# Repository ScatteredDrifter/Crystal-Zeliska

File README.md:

# Crystal-Zeliska
---
##### <div align="right">Created and designed by: Fabian.S || ScatteredDrifter
</div>
<br />
<br/>
Welcome my first attempt to design a orthogonal split-keyboard. 

This is a 62-key-keyboard with 31 1u keys per side. 

The PCB was designed to be usable for both the left and right side. 

## Features: 
 - offers OLED - SSD1306 - display support, at least in theory **#** *haven't tested it yet* 
 - eight ws2812b mounted RGB LEds for underglow around the keyboard
 - included files for bottom and top-plate for FR4 skeleton mounting method

## Planned Features: 

- QMK support
- updated PCB with support pimoroni trackball 
- support for rotary encoder 
- acrylic stand offs for pro micros **#** *needs revision of pcb design*
- battery mount and charging circuit on pcb / or on smaller additional pcb
- 3d printable case | -  flat / high  **#** *add support for tenting*

## Images: 

**Right side of PCB**

**Left side of PCB**

---

**|| - Glory To mankind**

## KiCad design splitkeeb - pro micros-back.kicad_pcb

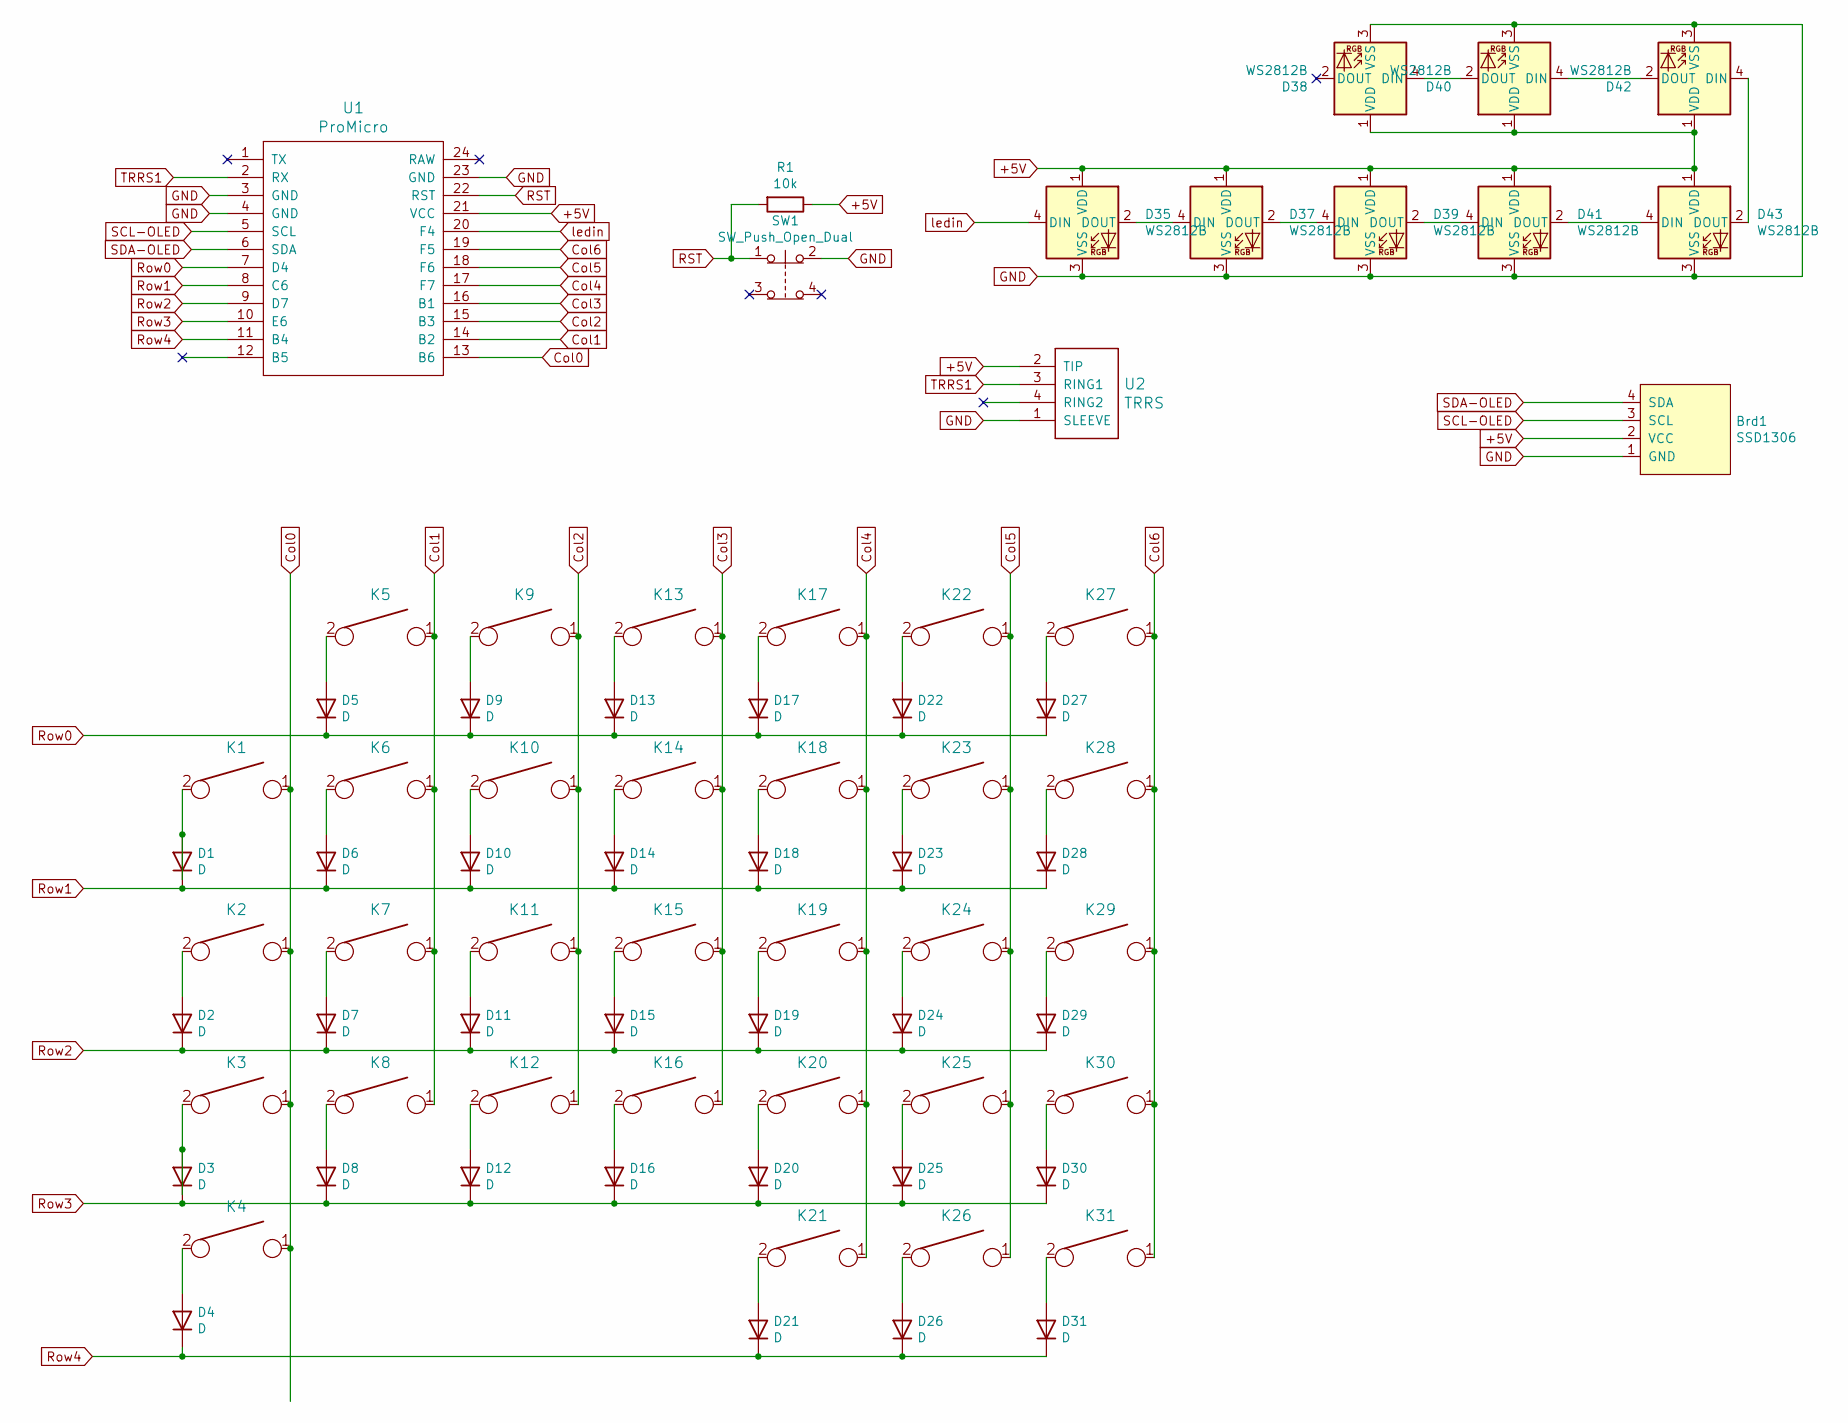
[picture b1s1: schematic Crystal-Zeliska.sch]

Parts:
Brd1: SSD1306; OLED
D1, D2, D3, D4, D5, D6, D7, D8, D9, D10, D11, D12, D13, D14, D15, D16, D17, D18, D19, D20, D21, D22, D23, D24, D25, D26, D27, D28, D29, D30, D31: D; D_SOD123_axial
D35, D37, D38, D39, D40, D41, D42, D43: WS2812B; LED_WS2812B_PLCC4_5.0x5.0mm_P3.2mm
K1, K2, K3, K4, K5, K6, K7, K8, K9, K10, K11, K12, K13, K14, K15, K16, K17, K18, K19, K20, K21, K22, K23, K24, K25, K26, K27, K28, K29, K30, K31: KEYSW; SW_MX_reversible
R1: 10k; Resistor-Hybrid
SW1: SW_Push_Open_Dual; SW_SPST_TL3342
U1: ProMicro
U2: TRRS; TRRS-PJ-320A

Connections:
/+5V: Brd1.2 (VCC), D35.1 (VDD), D37.1 (VDD), D38.1 (VDD), D39.1 (VDD), D40.1 (VDD), D41.1 (VDD), D42.1 (VDD), D43.1 (VDD), R1.1, U1.21 (VCC), U2.2 (TIP); also elsewhere on the board
/GND: Brd1.1 (GND), D35.3 (VSS), D37.3 (VSS), D38.3 (VSS), D39.3 (VSS), D40.3 (VSS), D41.3 (VSS), D42.3 (VSS), D43.3 (VSS), SW1.2, U1.3 (GND), U1.4 (GND), U1.23 (GND), U2.1 (SLEEVE); also elsewhere on the board
/RST: R1.2, SW1.1, U1.22 (RST); also elsewhere on the board
/SCL-OLED: Brd1.3 (SCL), U1.5 (SCL); also elsewhere on the board
/SDA-OLED: Brd1.4 (SDA), U1.6 (SDA); also elsewhere on the board
/TRRS1: U1.2 (RX), U2.3 (RING1); also elsewhere on the board
/col0: K1.1, K2.1, K3.1, K4.1, U1.13 (B6); also elsewhere on the board
/col1: K5.1, K6.1, K7.1, K8.1, U1.14 (B2); also elsewhere on the board
/col2: K9.1, K10.1, K11.1, K12.1, U1.15 (B3); also elsewhere on the board
/col3: K13.1, K14.1, K15.1, K16.1, U1.16 (B1); also elsewhere on the board
/col4: K17.1, K18.1, K19.1, K20.1, K21.1, U1.17 (F7); also elsewhere on the board
/col5: K22.1, K23.1, K24.1, K25.1, K26.1, U1.18 (F6); also elsewhere on the board
/col6: K27.1, K28.1, K29.1, K30.1, K31.1, U1.19 (F5); also elsewhere on the board
/ledin: D35.4 (DIN), U1.20 (F4); also elsewhere on the board
/row0: D5.1 (K), D9.1 (K), D13.1 (K), D17.1 (K), D22.1 (K), D27.1 (K), U1.7 (D4); also elsewhere on the board
/row1: D1.1 (K), D6.1 (K), D10.1 (K), D14.1 (K), D18.1 (K), D23.1 (K), D28.1 (K), U1.8 (C6); also elsewhere on the board
/row2: D2.1 (K), D7.1 (K), D11.1 (K), D15.1 (K), D19.1 (K), D24.1 (K), D29.1 (K), U1.9 (D7); also elsewhere on the board
/row3: D3.1 (K), D8.1 (K), D12.1 (K), D16.1 (K), D20.1 (K), D25.1 (K), D30.1 (K), U1.10 (E6); also elsewhere on the board
/row4: D4.1 (K), D21.1 (K), D26.1 (K), D31.1 (K), U1.11 (B4); also elsewhere on the board
unnamed: D1.2 (A), K1.2
unnamed: D2.2 (A), K2.2
unnamed: D3.2 (A), K3.2
unnamed: D4.2 (A), K4.2
unnamed: D5.2 (A), K5.2
unnamed: D6.2 (A), K6.2
unnamed: D7.2 (A), K7.2
unnamed: D8.2 (A), K8.2
unnamed: D9.2 (A), K9.2
unnamed: D10.2 (A), K10.2
unnamed: D11.2 (A), K11.2
unnamed: D12.2 (A), K12.2
unnamed: D13.2 (A), K13.2
unnamed: D14.2 (A), K14.2
unnamed: D15.2 (A), K15.2
unnamed: D16.2 (A), K16.2
unnamed: D17.2 (A), K17.2
unnamed: D18.2 (A), K18.2
unnamed: D19.2 (A), K19.2
unnamed: D20.2 (A), K20.2
unnamed: D21.2 (A), K21.2
unnamed: D22.2 (A), K22.2
unnamed: D23.2 (A), K23.2
unnamed: D24.2 (A), K24.2
unnamed: D25.2 (A), K25.2
unnamed: D26.2 (A), K26.2
unnamed: D27.2 (A), K27.2
unnamed: D28.2 (A), K28.2
unnamed: D29.2 (A), K29.2
unnamed: D30.2 (A), K30.2
unnamed: D31.2 (A), K31.2
unnamed 50: D35.2 (DOUT), D37.4 (DIN); also elsewhere on the board
unnamed 51: D37.2 (DOUT), D39.4 (DIN); also elsewhere on the board
unnamed 52: D38.2 (DOUT); also elsewhere on the board
unnamed 53: D38.4 (DIN), D40.2 (DOUT); also elsewhere on the board
unnamed 54: D39.2 (DOUT), D41.4 (DIN); also elsewhere on the board
unnamed 55: D40.4 (DIN), D42.2 (DOUT); also elsewhere on the board
unnamed 56: D41.2 (DOUT), D43.4 (DIN); also elsewhere on the board
unnamed 57: D42.4 (DIN), D43.2 (DOUT); also elsewhere on the board
unnamed 58: U1.1 (TX); also elsewhere on the board
unnamed 59: U1.12 (B5); also elsewhere on the board
unnamed 60: U1.24 (RAW); also elsewhere on the board

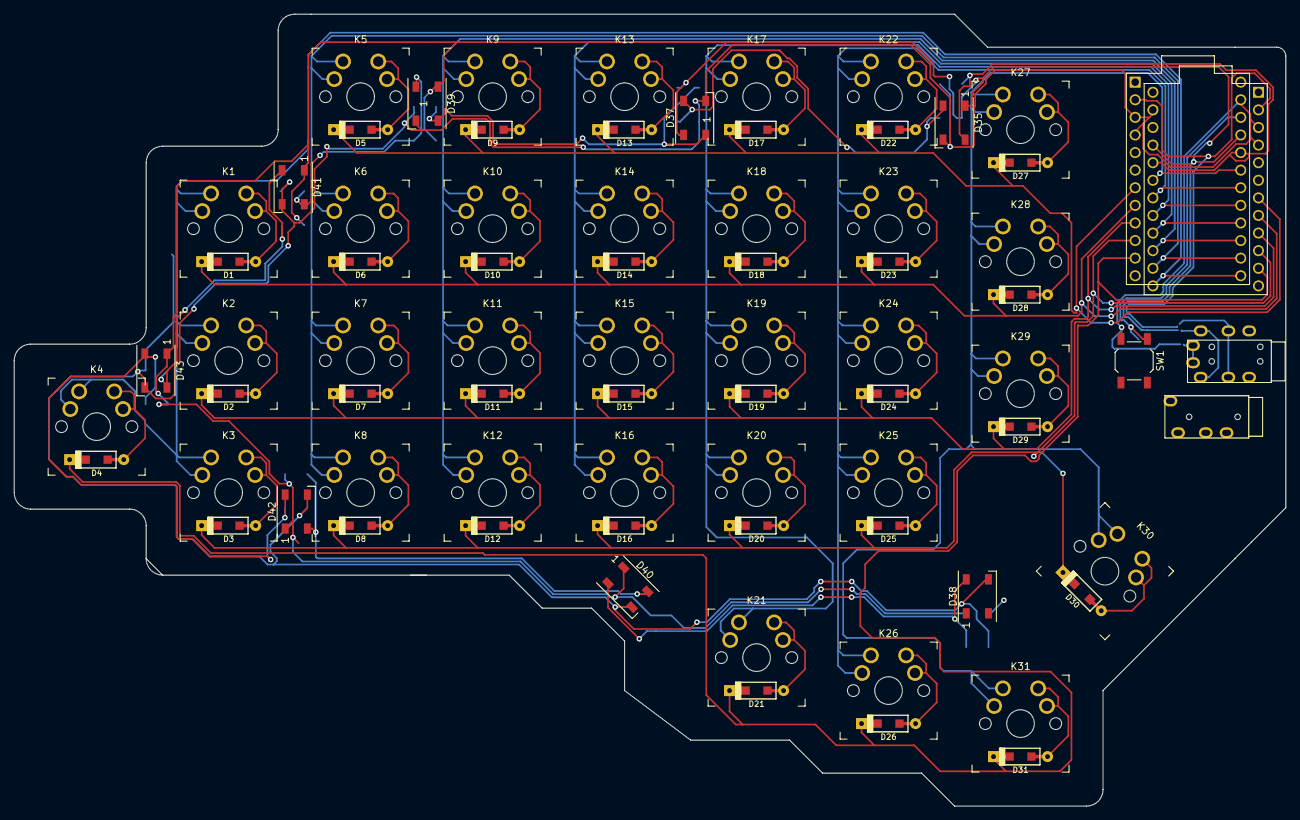
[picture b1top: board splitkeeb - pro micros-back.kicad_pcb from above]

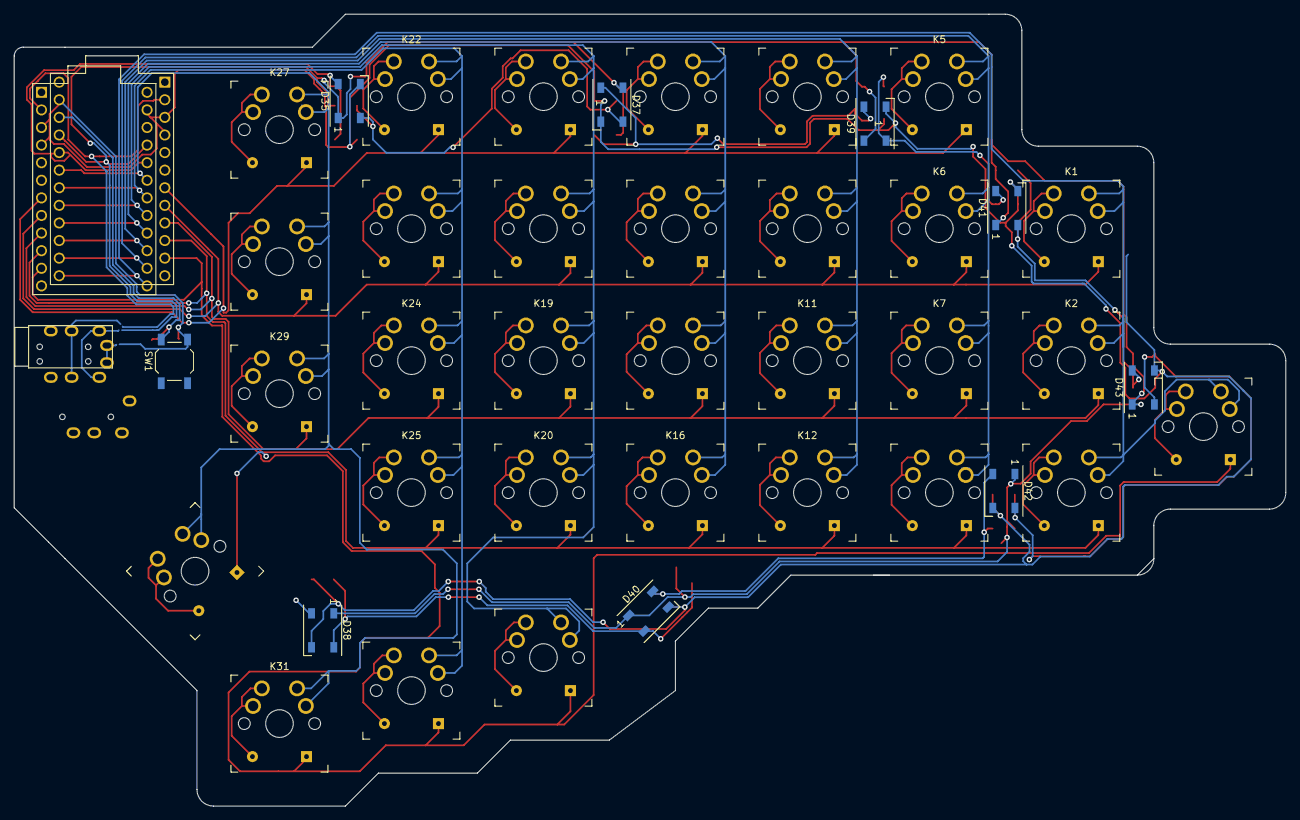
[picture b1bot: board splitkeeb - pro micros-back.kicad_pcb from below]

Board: 2 copper layers, 183.5 x 114.3 mm, 85 parts (11 on the bottom side), 61 nets.

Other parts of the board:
D35#2, D37#2, D38#2, D39#2, D40#2, D41#2, D42#2, D43#2: WS2812B; LED_WS2812B_PLCC4_5.0x5.0mm_P3.2mm
J1, J1#2, J1#3: AudioJack4; TRRS-PJ-320A
SW1#2: SW_Push_Open_Dual; SW_SPST_TL3342
U1#2: ProMicro

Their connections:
/+5V: D35#2.1, D37#2.1, D38#2.1, D39#2.1, D40#2.1, D41#2.1, D42#2.1, D43#2.1, U1#2.21; also elsewhere on the board
/GND: D35#2.3, D37#2.3, D38#2.3, D39#2.3, D40#2.3, D41#2.3, D42#2.3, D43#2.3, SW1#2.2, U1#2.3, U1#2.4, U1#2.23; also elsewhere on the board
/RST: SW1#2.1, U1#2.22; also elsewhere on the board
/SCL-OLED: U1#2.5; also elsewhere on the board
/SDA-OLED: U1#2.6; also elsewhere on the board
/TRRS1: U1#2.2; also elsewhere on the board
/col0: U1#2.13; also elsewhere on the board
/col1: U1#2.14; also elsewhere on the board
/col2: U1#2.15; also elsewhere on the board
/col3: U1#2.16; also elsewhere on the board
/col4: U1#2.17; also elsewhere on the board
/col5: U1#2.18; also elsewhere on the board
/col6: U1#2.19; also elsewhere on the board
/ledin: D35#2.4, U1#2.20; also elsewhere on the board
/row0: U1#2.7; also elsewhere on the board
/row1: U1#2.8; also elsewhere on the board
/row2: U1#2.9; also elsewhere on the board
/row3: U1#2.10; also elsewhere on the board
/row4: U1#2.11; also elsewhere on the board
unnamed 50: D35#2.2, D37#2.4; also elsewhere on the board
unnamed 51: D37#2.2, D39#2.4; also elsewhere on the board
unnamed 52: D38#2.2; also elsewhere on the board
unnamed 53: D38#2.4, D40#2.2; also elsewhere on the board
unnamed 54: D39#2.2, D41#2.4; also elsewhere on the board
unnamed 55: D40#2.4, D42#2.2; also elsewhere on the board
unnamed 56: D41#2.2, D43#2.4; also elsewhere on the board
unnamed 57: D42#2.4, D43#2.2; also elsewhere on the board
unnamed 58: U1#2.1; also elsewhere on the board
unnamed 59: U1#2.12; also elsewhere on the board
unnamed 60: U1#2.24; also elsewhere on the board

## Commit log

2021-04-05 First commit, fundamental files
    - further structure mandatory
    - update Pcb - add images, own stamps
2021-04-06 Second commit, updated plate,pcb,bottom, cleaned file etc
2021-04-07 newer bottom-plate, test-gerber for bottom plates, some improvements regarding file structure
2021-04-08 updated pcb, deleted obsolete files
2021-04-09 updated pcb
2021-04-17 updated Gerber
2021-04-18 updated PCb with m2.2mm screws
